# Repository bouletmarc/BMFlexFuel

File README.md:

# BMFlexFuel
BMDevs Flex Fuel Adapter Project

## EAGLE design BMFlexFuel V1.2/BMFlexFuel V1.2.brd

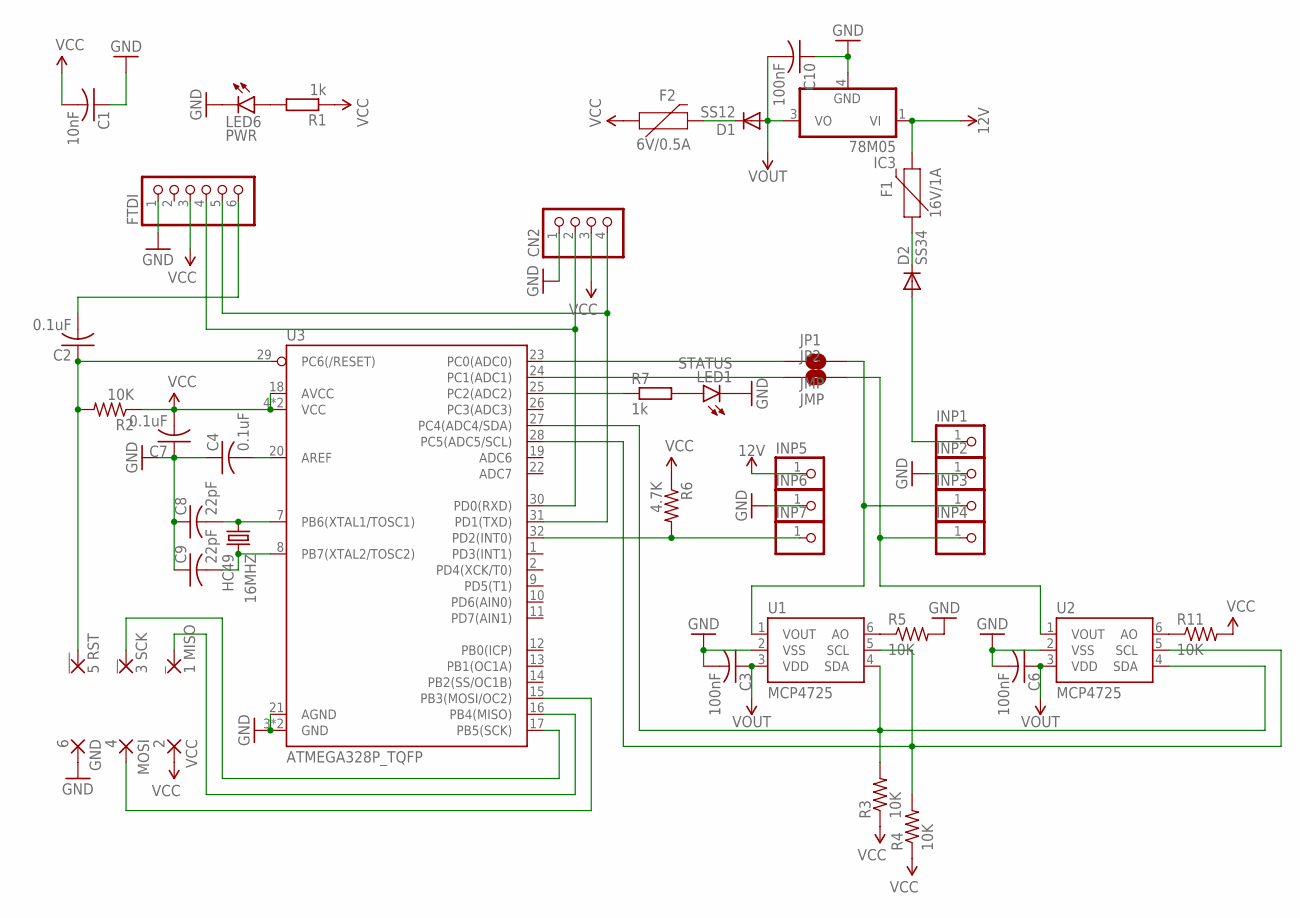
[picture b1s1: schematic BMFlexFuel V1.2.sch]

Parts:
16MHZ: HC49
C1: 10nF; C1206
C2, C4, C7: 0.1uF; C0603
C3, C6, C10: 100nF; C0603
C8, C9: 22pF; C0603
CN2: PINHD-1X4; 1X04
D1: SS12; DO214AC
D2: SS34; DO214AC
F1: 16V/1A; 1206
F2: 6V/0.5A; 1206
FTDI: PINHD-1X6; 1X06
GND: 6; SMD1,27-2,54
IC3: 78M05; DPACK_3
INP1, INP2, INP3, INP4, INP5, INP6, INP7: PINHD-1X1_LARGE; 1X01_LARGE
JP1, JP2: JMP; SMT-JUMPER_2_NO_NO-SILK
LED1: STATUS; CHIPLED_0805
LED6: PWR; CHIPLED_0805
MOSI: 4; SMD1,27-2,54
R1, R7: 1k; R0603
R2, R3, R4, R5, R11: 10K; R0603@1
R6: 4.7K; R0603@1
U1, U2: MCP4725; SOT23-6
U3: ATMEGA328P_TQFP; TQFP32-08
VCC: 2; SMD1,27-2,54
_: 1 MISO; SMD1,27-2,54
__: 3 SCK; SMD1,27-2,54
___: 5 RST; SMD1,27-2,54

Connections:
12V: F1.2, IC3.1 (VI), INP5.1
GND: C1.1, C3.2, C4.1, C6.2, C7.1, C8.1, C9.1, C10.1, CN2.1, FTDI.1, GND.1, IC3.4 (GND), INP2.1, INP6.1, LED1.C, LED6.C, R5.2, U1.2 (VSS), U2.2 (VSS), U3.3 (GND), U3.5 (GND), U3.21 (AGND)
unnamed: INP7.1, R6.2, U3.32 (PD2(INT0))
unnamed: D2.C, F1.1
unnamed: JP1.1, U3.23 (PC0(ADC0))
unnamed: R3.2, U1.4 (SDA), U2.4 (SDA), U3.27 (PC4(ADC4/SDA))
unnamed: LED6.A, R1.2
unnamed: D1.C, F2.2
unnamed: JP2.1, U3.24 (PC1(ADC1))
unnamed: LED1.A, R7.2
unnamed: R7.1, U3.25 (PC2(ADC2))
unnamed: R5.1, U1.6 (AO)
unnamed: R11.1, U2.6 (AO)
unnamed: C2.1, R2.2, U3.29 (PC6(/RESET)), ___.1
unnamed: D2.A, INP1.1
unnamed: C4.2, U3.20 (AREF)
unnamed: 16MHZ.1, C8.2, U3.7 (PB6(XTAL1/TOSC1))
unnamed: INP3.1, JP1.2, U1.1 (VOUT)
unnamed: C2.2, FTDI.6
unnamed: INP4.1, JP2.2, U2.1 (VOUT)
unnamed: R4.2, U1.5 (SCL), U2.5 (SCL), U3.28 (PC5(ADC5/SCL))
unnamed: 16MHZ.2, C9.2, U3.8 (PB7(XTAL2/TOSC2))
unnamed: CN2.2, FTDI.4, U3.30 (PD0(RXD))
unnamed: CN2.4, FTDI.5, U3.31 (PD1(TXD))
unnamed: U3.17 (PB5(SCK)), __.1
unnamed: U3.16 (PB4(MISO)), _.1
unnamed: MOSI.1, U3.15 (PB3(MOSI/OC2))
VCC: C1.2, C7.2, CN2.3, F2.1, FTDI.3, R1.1, R2.1, R3.1, R4.1, R6.1, R11.2, U3.4 (VCC), U3.6 (VCC), U3.18 (AVCC), VCC.1
VOUT: C3.1, C6.1, C10.2, D1.A, IC3.3 (VO), U1.3 (VDD), U2.3 (VDD)

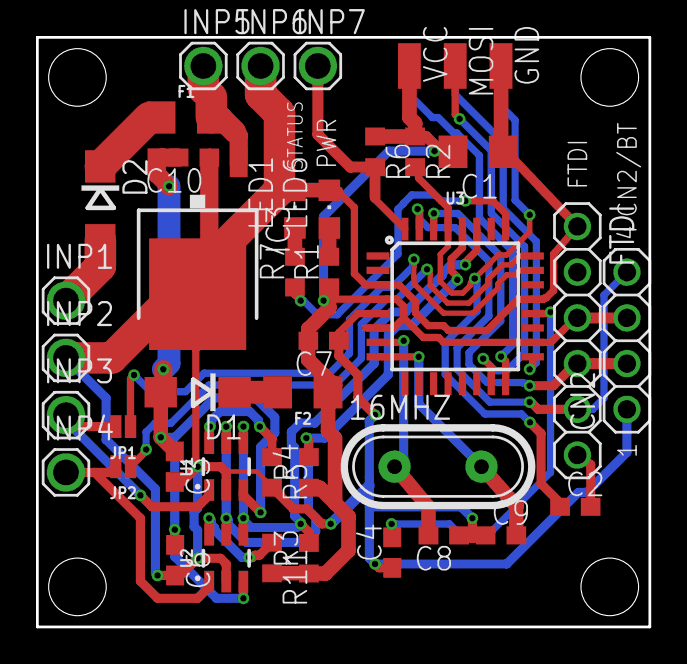
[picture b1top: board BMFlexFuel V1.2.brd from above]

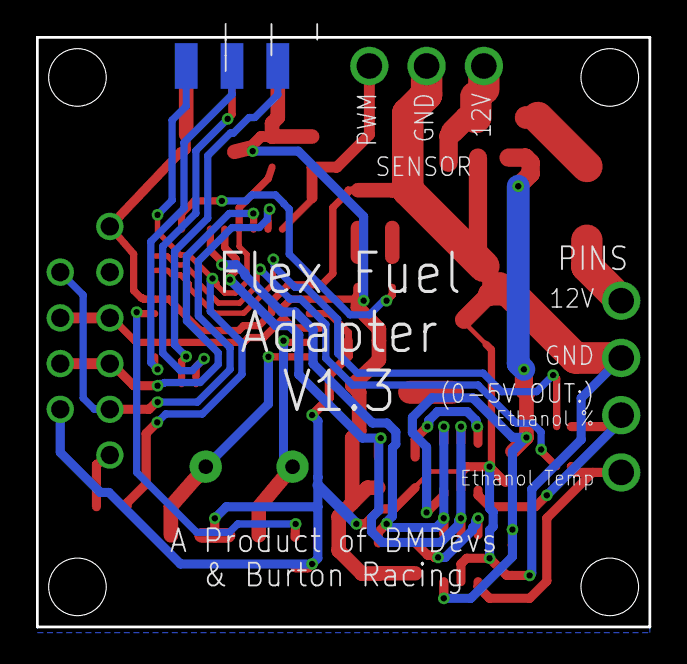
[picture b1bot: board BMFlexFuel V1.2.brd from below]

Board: 2 copper layers, 34.0 x 32.8 mm, 45 parts (3 on the bottom side), 29 nets.

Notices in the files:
parts and their libraries:
SparkFun-Fuses: Licensing: Creative Commons ShareAlike 4.0 International - https://creativecommons.org/licenses/by-sa/4.0
SparkFun: Licensing: CC v3.0 Share-Alike You are welcome to use this library for commercial purposes.
